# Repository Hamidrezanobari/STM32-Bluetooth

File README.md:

# STM32 Bluetooth Development Board (stm32withBluetooth)

**A compact STM32WB55-based development board with USB-C, designed for BLE-enabled embedded projects.**

---

## At-a-glance
- **Main MCU:** STM32WB55CEU6 (Cortex-M4 + BLE radio). (Ref: `U3`)
- **Power:** MIC5365-3.3YD5 linear regulators (3.3V). (Refs: `U`, `U2`)
- **Clocking:** 32 MHz crystal + 32.768 kHz RTC crystal
- **Connectivity:** USB Type-C connector (power / USB2.0)
- **Debugging:** SWD Tag-Connect footprint (TC2030)
- **Peripherals:** LEDs, push-button, mounting holes, fiducials
- **Special footprints:** Bluetooth-specific footprint / antenna footprint present (`bluetoothLib` folder)
- **Outputs included:** KiCad schematic (`*.kicad_sch`), PCB (`*.kicad_pcb`), footprints (`*.pretty`), 3D STEP models, and Gerbers under `Manufacturing/`.

---

## Contents of this repository
```
/stm32withBlueto0th.kicad_sch        # KiCad schematic
/stm32withBlueto0th.kicad_pcb        # KiCad PCB file
/*.pretty/                           # custom footprints (including bluetooth footprint)
3D/                                  # STEP models (STM32WB, crystals, etc.)
Manufacturing/                       # Gerber files for PCB manufacturing
/stm32withBlueto0th-backups/         # backup ZIPs and prior versions
README.md (this file)
```

---

## Key components (auto-detected / inferred)
> Below are the main parts identified in the schematic. Reference names follow the schematic where available.

- **U3** — `STM32WB55CEU6` (main MCU with integrated BLE radio)  
- **U**, **U2** — `MIC5365-3.3YD5` (3.3V LDO regulators)  
- **J1** — `USB_C_Receptacle_USB2.0_16P` (USB-C connector footprint)  
- **J2** — `Conn_ARM_SWD_TagConnect_TC2030` (SWD / Tag-Connect debug header)  
- **X1** — `32 MHz crystal` (main oscillator for MCU)  
- **Y? / FLT** — `32.768 kHz` (RTC crystal footprint present; 3D models show `NX2012SA-32.768K`)  
- **DLF162500LT-5028A1** — footprint present in `bluetoothLib` (likely antenna or related footprint)  
- Passive components: decoupling caps (100nF etc.), bulk caps (4.7uF), resistors (5k1, 220R, ...), inductors (L - power/filter), LEDs, push-button (SW)  
- Mechanical: mounting holes, fiducials, board outline and edge cuts (Gerbers included)

---

## Board functions & intended use
This board appears designed as a small STM32WB55 development / application board for BLE-enabled projects that require:
- USB (power / potential USB data),
- programming via SWD Tag-Connect or USB DFU (if firmware supports it),
- RTC support (32.768 kHz crystal),
- on-board antenna footprint / matching network for BLE,
- stable 3.3V supply from onboard LDO(s).

Use-cases: BLE peripherals, sensor nodes, gateway prototypes (with additional modules), low-power development.

---

## How to build and flash (recommended workflow)

### 1. Open the project
- Use **KiCad (2024/2025)** — the schematic/pcb files indicate KiCad 2024/2025 file formats.  
- Open `stm32withBlueto0th.kicad_sch` in Eeschema and `stm32withBlueto0th.kicad_pcb` in Pcbnew.

### 2. Generate BOM & Gerbers
- BOM (CSV): Eeschema → Generate BOM (or run a script to parse `*.kicad_sch`).  
- Gerbers already provided under `Manufacturing/` if you want to order boards.

### 3. Programming options
- **SWD Tag-Connect**: Use an ST-LINK (or any SWD programmer) with a Tag-Connect cable connected to the TC2030 footprint (`J2`). If no TC cable, use small wires to the labelled SWD pads.  
- **USB DFU (optional)**: If firmware implements USB DFU (and USB lines are connected to MCU's USB pins & VBUS detection), you can flash via DFU over USB-C. Verify schematic that MCU USB D+/D- are connected correctly and that VBUS is present on the USB connector.  
- **Toolchain:** Use **STM32CubeIDE** or GCC arm toolchain + STM32CubeWB middleware (for wireless stacks). STM32CubeWB package contains BLE stack examples for STM32WB series.

### 4. Flashing steps (example using ST-LINK + STM32CubeIDE)
1. Connect ST-LINK to the Tag-Connect footprint (or SWD wires).  
2. Open or create the firmware project in STM32CubeIDE (select MCU: STM32WB55CEUx).  
3. Build and Run → Debug to program flash.

---

## Notes, observations & suggestions (from analysis)
1. **No CAN:** If your aim is automotive / CAN interfacing, add an external CAN transceiver (e.g. SN65HVD230) and a CAN connector (DB9/OBD or screw terminal) plus 120Ω termination. STM32WB has CAN only on some MCU families — double-check pin availability or switch to an STM32 with bxCAN if heavy CAN work is planned (e.g., STM32F1/F4/F7 families or some F4/F7 parts with CAN).  
2. **Antenna / RF:** Project contains Bluetooth footprint and 3D part models. Verify antenna keepout, matching network, and ground plane per STM32WB datasheet and antenna vendor recommendations before mass-production. RF layout rules matter!  
3. **Power:** Two MIC5365 LDOs appear — ensure proper decoupling and thermal consideration. If you need low-power sleep modes for BLE, consider using low-Iq regulator or switch to buck converter for higher efficiency depending on current draw.  
4. **USB:** If you plan USB device functionality, ensure ESD and VBUS protection components are present (TVS, VBUS resistors). I saw VBUS nets in schematic; double-check for differential pair routing and correct USB pull-up/pull-down resistors if needed.  
5. **Test points & silkscreen:** Add clear test points for SWD, VCC, GND, and important signals for easier debugging/manufacturing testing.

---

## Next steps I can do for you (choose one or more)
- [ ] Generate a **detailed BOM (CSV)** automatically from the schematic (refs, values, footprints).  
- [ ] Extract a **component list with footprints** and produce a printable BOM + place file.  
- [ ] Produce a **hardware overview section** with annotated PCB screenshots (I can create PNGs of the PCB from the KiCad files if you want).  
- [ ] Add a **“How to flash”** step-by-step with exact pinouts for Tag-Connect and example STM32CubeIDE project skeleton (I can also provide a sample `main.c`).  
- [ ] Convert README to **dual-language (English + Persian)**.

---

## License
Add your preferred license file to the repo. If you want, I can add a recommended license (e.g., MIT) and include it in the README.

---

## Author
Your name (please replace): **_Your Name Here_**  
Auto-generated analysis performed by script on included KiCad project files (`stm32withBlueto0th.zip`).

---

### Quick disclaimer
This README and the component identification were autogenerated by parsing the KiCad schematic and PCB files in this zip. Some values/footprints (e.g., custom footprints, exact antenna tuning components) might require manual verification. If you want, I can produce a fully verified BOM by cross-checking every symbol in the schematic and matching footprints—tell me and I’ll generate it next.

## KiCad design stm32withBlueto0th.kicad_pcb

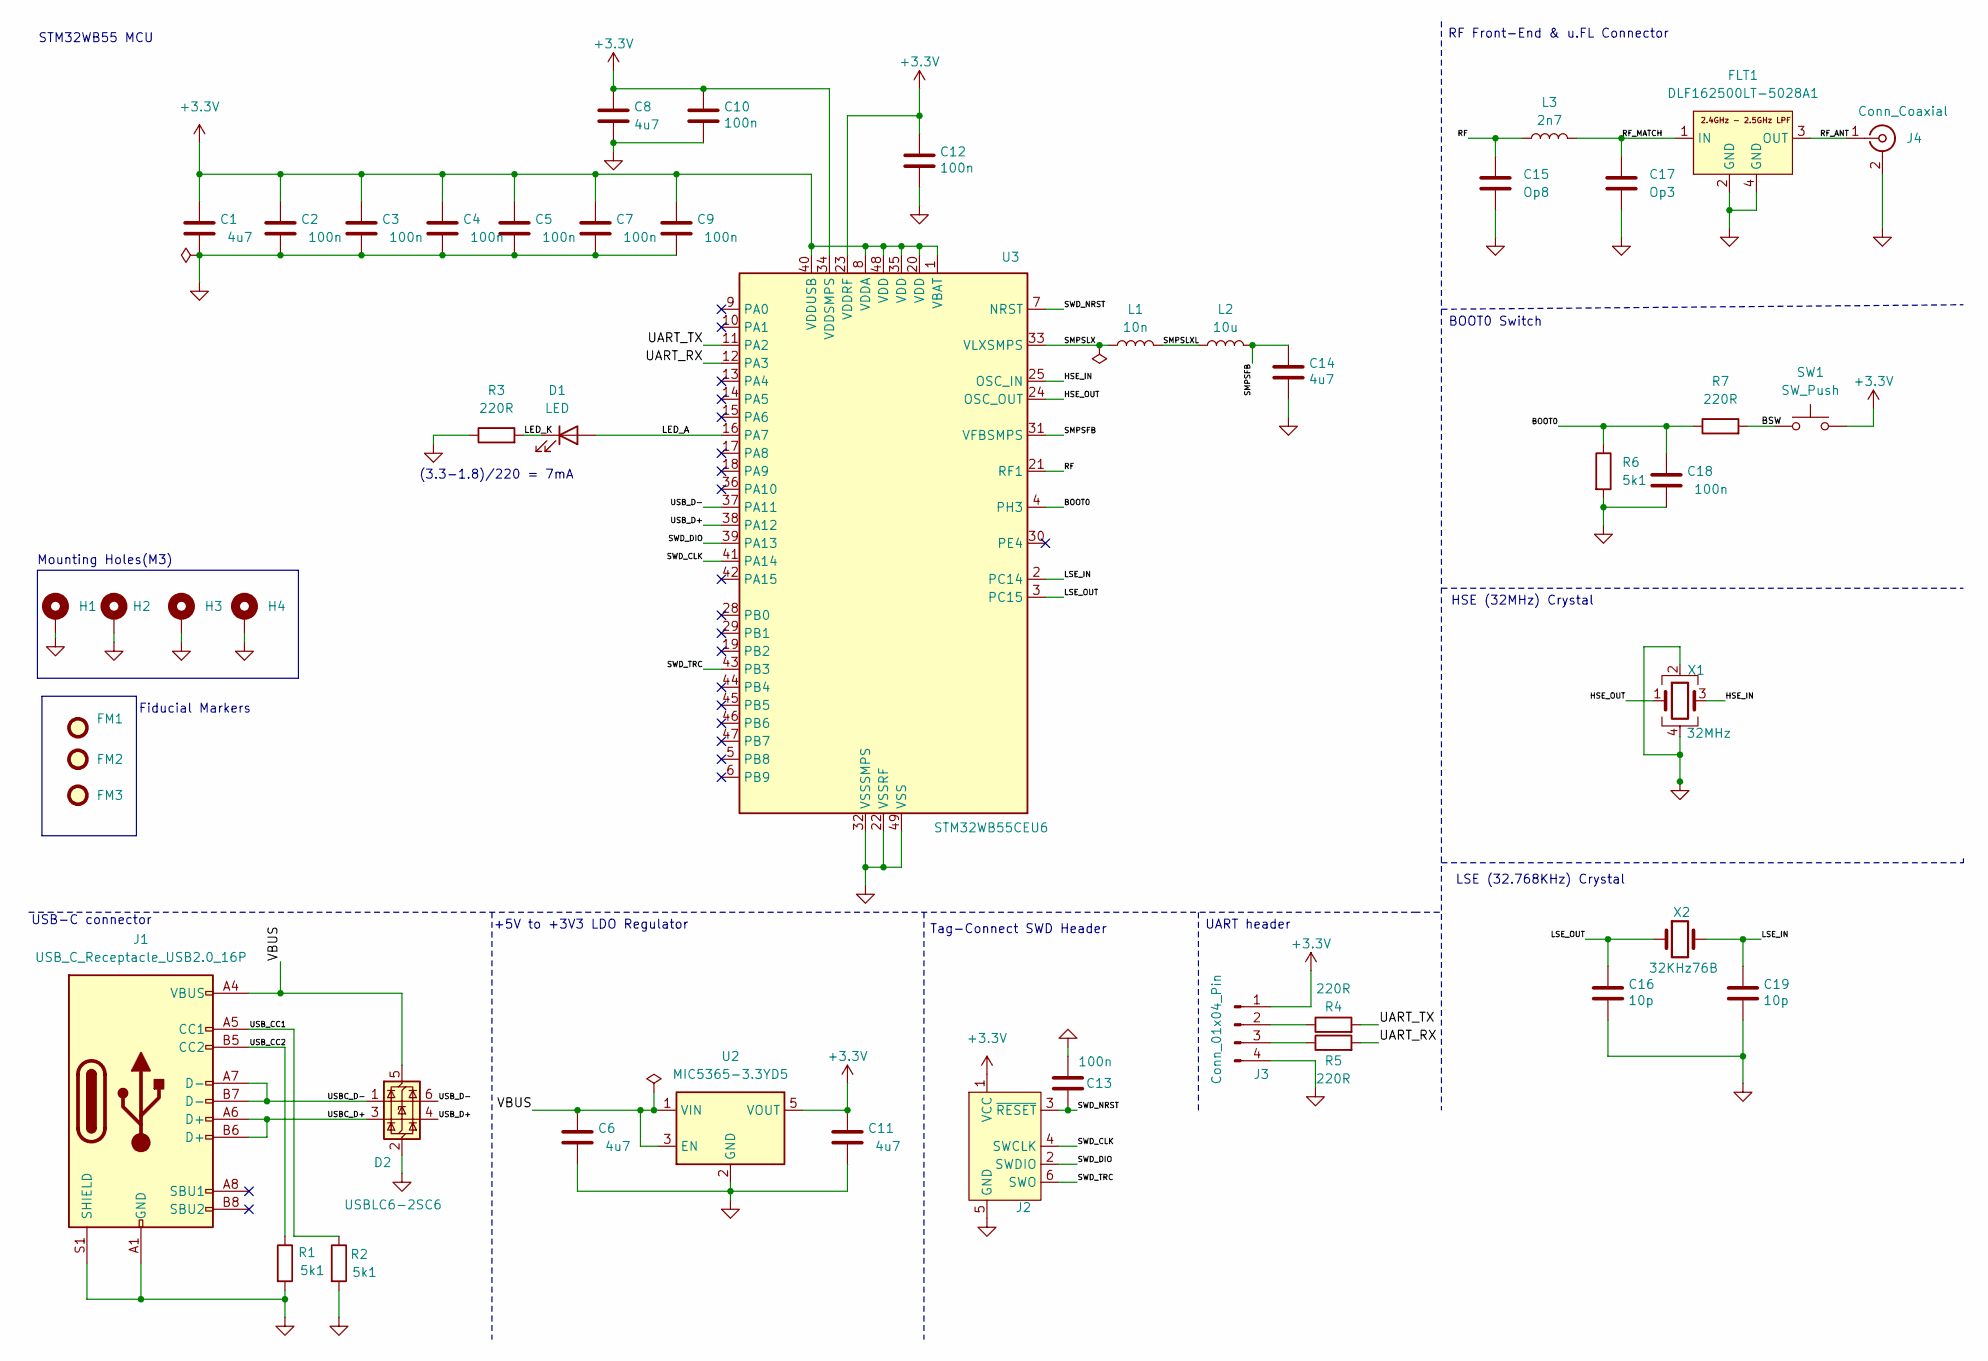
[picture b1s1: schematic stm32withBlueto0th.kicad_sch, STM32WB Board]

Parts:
C1, C6, C8, C11, C14: 4u7; C_0603_1608Metric; Manufacturere part numb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 0603YD475MAT2A
C2, C3, C4, C5, C7, C9, C10, C12, C13, C18: 100n; C_0402_1005Metric; Manufacturere part numb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 04023C104KAT2A
C15: Op8; C_0402_1005Metric; Manufacturere part numb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 GRM1555C1HR80BA01D
C16, C19: 10p; C_0402_1005Metric; Manufacturere part numb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 04025A100JAT4A
C17: Op3; C_0402_1005Metric; Manufacturere part numb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 GRM1555C1HR30WA01D
D1: LED; LED_01005_0402Metric; Manufacturere part numb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 150040RS73240
D2: USBLC6-2SC6; SOT-23-6; Manufacturere part numb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 USBLC6-2SC6
FLT1: DLF162500LT-5028A1; Manufacturere part numb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 DLF162500LT-5028A1
FM1, FM2, FM3: Fiducial; Fiducial_1mm_Mask2mm
H1, H2, H3, H4: MountingHole_Pad; MountingHole_2.2mm_M2_Pad
J1: USB_C_Receptacle_USB2.0_16P; USB_C_Receptacle_GCT_USB4105-xx-A_16P_TopMnt_Horizontal; Manufacturere part numb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 USB4105-GF-A
J2: Conn_ARM_SWD_TagConnect_TC2030; Tag-Connect_TC2030-IDC-FP_2x03_P1.27mm_Vertical
J3: Conn_01x04_Pin; Molex_PicoBlade_53048-0410_1x04_P1.25mm_Horizontal; Manufacturere part numb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 53048-0410
J4: Conn_Coaxial; U.FL_Hirose_U.FL-R-SMT-1_Vertical; Manufacturere part numb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 U.FL-R-SMT(01)
L1: 10n; L_0402_1005Metric; Manufacturere part numb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 LQG15WZ10NJ02D
L2: 10u; L_0805_2012Metric; Manufacturere part numb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 LQM21FN100M70L
L3: 2n7; L_0402_1005Metric; Manufacturere part numb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 LQG15HS2N7S02
R1, R2, R6: 5k1; R_0402_1005Metric; Manufacturere part numb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 RC0603FR-075K1L
R3, R4, R5, R7: 220R; R_0402_1005Metric; Manufacturere part numb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 RC0402FR-07221RL
SW1: SW_Push; SW_SPST_CK_RS282G05A3; Manufacturere part numb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 RS282G05A3SMRT
U2: MIC5365-3.3YD5; TSOT-23-5; Manufacturere part numb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 MIC5365-3.3YD5-TR
U3: STM32WB55CEU6; QFN-48-1EP_7x7mm_P0.5mm_EP5.6x5.6mm; Manufacturere part numb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 STM32WB55CEU6
X1: 32MHz; Crystal_SMD_2016-4Pin_2.0x1.6mm; Manufacturere part numb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 NX2016SA-32M-EXS00A-CS06465
X2: 32KHz76B; Crystal_SMD_2012-2Pin_2.0x1.2mm; Manufacturere part numb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 NX2012SA-32.768K-STD-MUB-1

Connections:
+3.3V: C1.1, C2.1, C3.1, C4.1, C5.1, C7.1, C8.1, C9.1, C10.1, C11.1, C12.1, J2.1 (VCC), J3.1, SW1.2, U2.5 (VOUT), U3.1 (VBAT), U3.8 (VDDA), U3.20 (VDD), U3.23 (VDDRF), U3.34 (VDDSMPS), U3.35 (VDD), U3.40 (VDDUSB), U3.48 (VDD)
/BOOT0: C18.1, R6.1, R7.1, U3.4 (PH3)
/BSW: R7.2, SW1.1
/HSE_IN: U3.25 (OSC_IN), X1.3
/HSE_OUT: U3.24 (OSC_OUT), X1.1
/LED_A: D1.2 (A), U3.16 (PA7)
/LED_K: D1.1 (K), R3.2
/LSE_IN: C19.1, U3.2 (PC14), X2.2
/LSE_OUT: C16.1, U3.3 (PC15), X2.1
/RF: C15.1, L3.1, U3.21 (RF1)
/RF_ANT: FLT1.3 (OUT), J4.1 (In)
/RF_MATCH: C17.1, FLT1.1 (IN), L3.2
/SMPSFB: C14.1, L2.2, U3.31 (VFBSMPS)
/SMPSLX: L1.1, U3.33 (VLXSMPS)
/SMPSLXL: L1.2, L2.1
/SWD_CLK: J2.4 (SWCLK), U3.41 (PA14)
/SWD_DIO: J2.2 (SWDIO), U3.39 (PA13)
/SWD_NRST: C13.1, J2.3 (~RESET), U3.7 (NRST)
/SWD_TRC: J2.6 (SWO), U3.43 (PB3)
/UART_RX: R5.2, U3.12 (PA3)
/UART_TX: R4.2, U3.11 (PA2)
/USBC_D+: D2.3 (I/O2), J1.A6 (D+), J1.B6 (D+)
/USBC_D-: D2.1 (I/O1), J1.A7 (D-), J1.B7 (D-)
/USB_CC1: J1.A5 (CC1), R2.1
/USB_CC2: J1.B5 (CC2), R1.1
/USB_D+: D2.4 (I/O2), U3.38 (PA12)
/USB_D-: D2.6 (I/O1), U3.37 (PA11)
/VBUS: C6.1, D2.5 (VBUS), J1.A4 (VBUS), J1.A9 (VBUS), J1.B4 (VBUS), J1.B9 (VBUS), U2.1 (VIN), U2.3 (EN)
GND: C1.2, C2.2, C3.2, C4.2, C5.2, C6.2, C7.2, C8.2, C9.2, C10.2, C11.2, C12.2, C13.2, C14.2, C15.2, C16.2, C17.2, C18.2, C19.2, D2.2 (GND), FLT1.2 (GND), FLT1.4 (GND), H1.1, H2.1, H3.1, H4.1, J1.A1 (GND), J1.A12 (GND), J1.B1 (GND), J1.B12 (GND), J1.S1 (SHIELD), J2.5 (GND), J3.4, J4.2 (Ext), R1.2, R2.2, R3.1, R6.2, U2.2 (GND), U3.22 (VSSRF), U3.32 (VSSSMPS), U3.49 (VSS), X1.2, X1.4
unnamed: J3.2, R4.1
unnamed: J3.3, R5.1

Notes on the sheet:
Mounting Holes(M3)
+5V to +3V3 LDO Regulator
STM32WB55 MCU
UART header
(3.3-1.8)/220 = 7mA
RF Front-End & u.FL Connector
LSE (32.768KHz) Crystal
Tag-Connect SWD Header
USB-C connector
BOOT0 Switch
Fiducial Markers
HSE (32MHz) Crystal

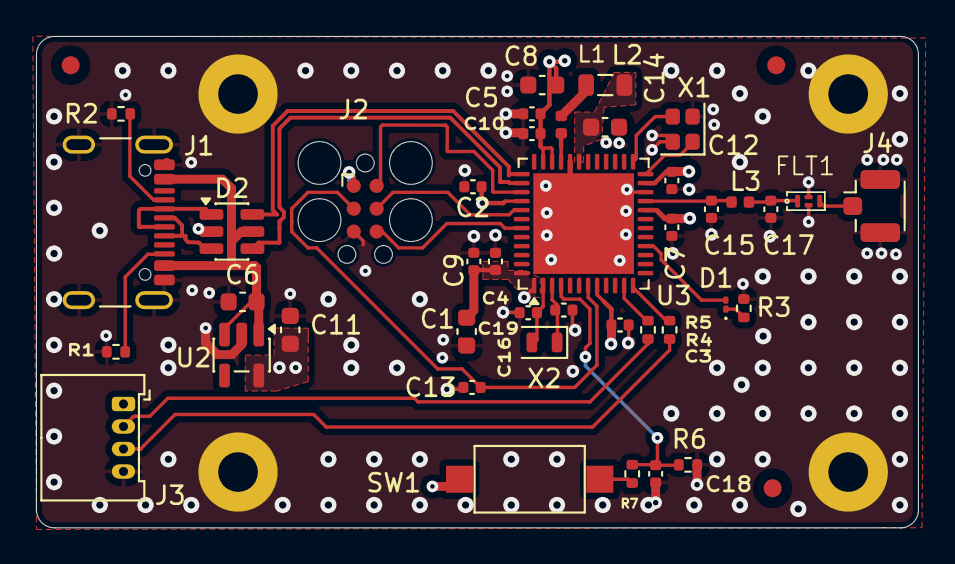
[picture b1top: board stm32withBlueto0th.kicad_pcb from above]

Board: 4 copper layers, 49.0 x 27.3 mm, 48 parts (0 on the bottom side), 31 nets.
